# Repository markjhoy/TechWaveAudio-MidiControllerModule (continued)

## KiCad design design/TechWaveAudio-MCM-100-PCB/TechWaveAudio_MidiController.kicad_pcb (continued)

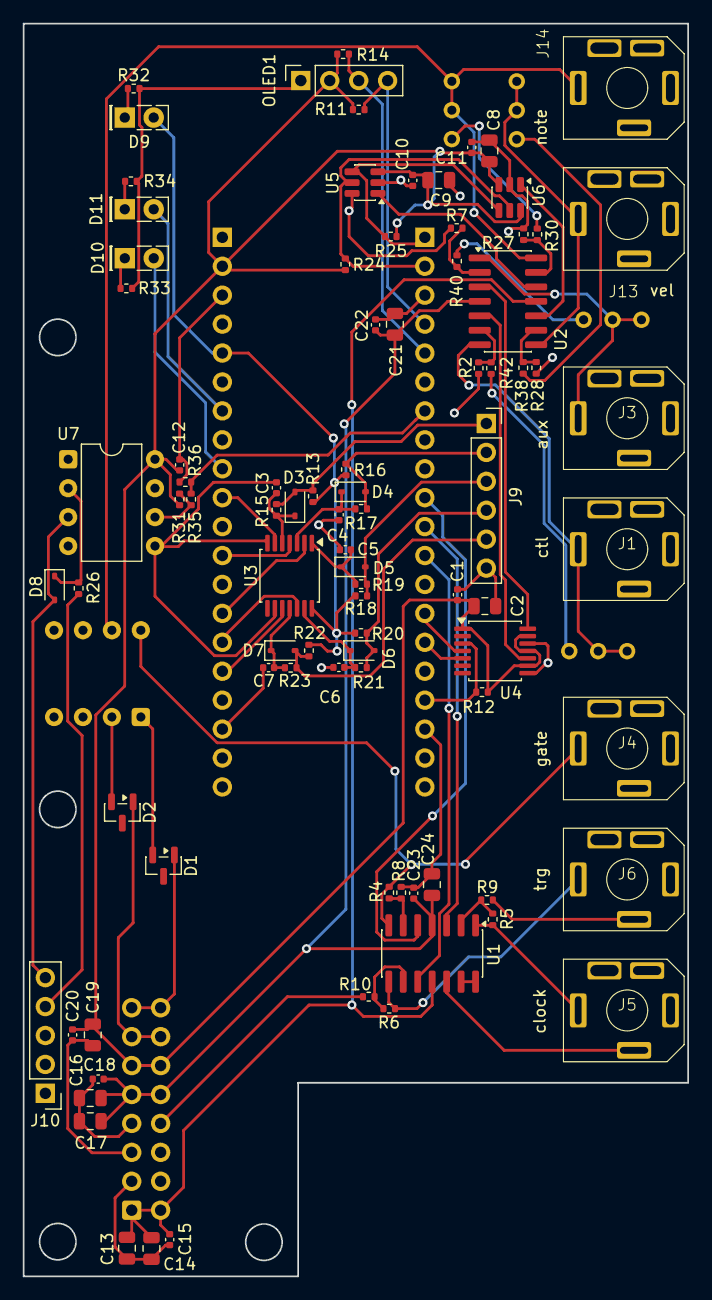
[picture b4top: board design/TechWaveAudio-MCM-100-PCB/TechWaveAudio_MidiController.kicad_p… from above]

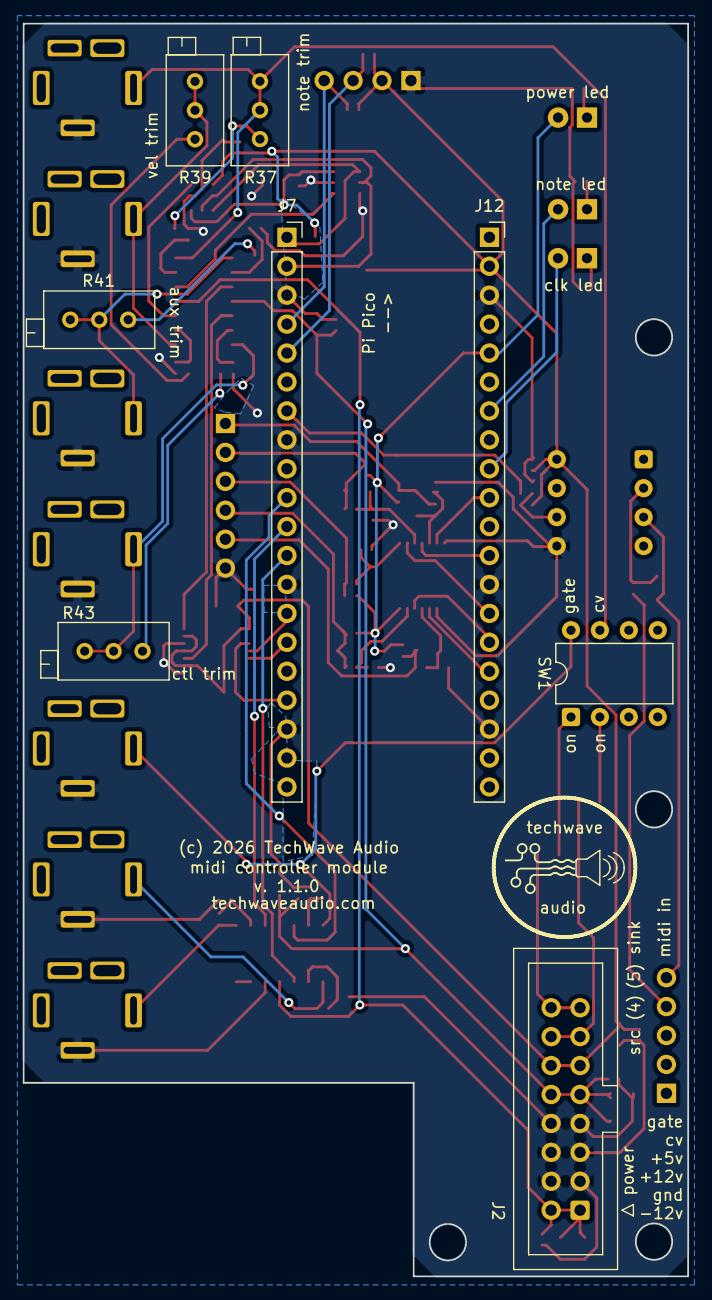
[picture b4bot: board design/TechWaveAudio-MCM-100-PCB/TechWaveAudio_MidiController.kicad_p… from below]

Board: 2 copper layers, 58.3 x 110.0 mm, 96 parts (8 on the bottom side), 67 nets.

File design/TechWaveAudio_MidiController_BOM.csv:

Surface Mount Components,,,,,,
ID,Qty,Description,Package,Mfgr,Mfg Part #,Link
"U5,U6",2,MCP4725 single channel 12 bit I2C DAC,SOIC-14,,,
"U1,U2",2,TL074 op amp,SOIC-14,,,
U4,1,MCP4902 dual channel 8 bit SPI DAC,TSSOP-14,,,
U3,1,40106 Hex Schmitt-trigger inverter,TSSOP-14,,,
"C1,C10,C11,C12,C15,C18 C20,C22,C23",9,100nf capacitor,SMD 0402,,,
"C2,C8,C9,C13,C14,C16,C17,C19,C21,C24",10,10uf capacitor (polarized),SMD 0805,,,
"C3,C4,C5,C6,C7",5,1uf capacitor,SMD 0402,,,
"D1,D2",2,Schottky diode (30v),SOT-23,,,
"D3,D4,D5,D6,D7,D8",6,1N4148 diode,D_SOD-323,,,
"R2 R4,R5,R6,R7,R27,R28,R35",8,resistor 5.1k,SMD 0402,,,
"R8,R9,R10,R36",4,resistor 10k,SMD 0402,,,
"R11,R14,R24,R25,R31",5,resistor 1k,SMD 0402,,,
"R12,R30,R38,R40,R42",5,resistor 4.7k,SMD 0402,,,
"R13,R16,R18,R20,R22",5,resistor 100k,SMD 0402,,,
"R15,R17,R19,R21,R23",5,resistor 220k,SMD 0402,,,
R26,1,resistor 220 ohm,SMD 0402,,,
"R32,R33,R34",3,resistor 330 ohm,SMD 0402,,,
,,,,,,
Through Hole Components,,,,,,
ID,Qty,Description,Mfgr,Mfg Part #,Link,
J2,1,16 pos 2x08 IDC pins (male),Samtec,TST-108-02-T-D,https://mou.sr/4oMjFmU,
"R37,R39,R41,R43",4,1k trim pot,Bourns,3296X-1-102LF,https://mou.sr/44u4OnX,
OLED1,1,1x04 socket connector,Samtec,SSW-104-01-T-S,https://mou.sr/43Qrwqd,
J9,1,1x06 socket connector,Samtec,SSW-106-01-T-S,https://mou.sr/4ahPiPr,
"J7,J12",2,1x20 socket connector,,,,
"J1,J3,J4,J5,J6,J13,J14",7,3.5mm Jack,,,,
SW1,1,4 position DIP switch,TE Connectivity,2454982-3,https://mou.sr/3SZFLqg,
--,1,5 way button,,,,
U7,1,6N137 Optocoupler,LITEON,6N137,https://mou.sr/4eIy9Qa,
D10,1,green LED,Kingbright,WP113GDT,https://mou.sr/4oNpEIp,
J10,1,MIDI jack,,,,
--,1,"0.96"" SSD1306-based I2C OLED",,,,
A1,1,Raspberry Pi Pico,Raspberry Pi,SC0917,https://mou.sr/41kRroA,
D9,1,red LED,Kingbright,WP113IDT,https://mou.sr/4xOIRNK,
D11,1,yellow LED,Kingbright,WP113YDT,https://mou.sr/4xOQVhs,
,,,,,,
Assembly Components,,,,,,
ID,Qty,Description,,,,
--,5,11mm PCB Standoff 3M hole,,,,
--,2,2M nut,,,,
--,2,2M x 8mm screw,,,,
--,6,3M nut,,,,
--,8,3M x 2mm spacer,(3d printed or bought),,,
--,10,3M x 5mm screw,,,,
--,6,3M x 8mm screw,,,,

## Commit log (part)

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2026-06-18 update default last note value
2026-06-23 working production hardware
2026-06-23 correct i2c / spi
2026-06-23 working multicore
2026-06-23 touch ups
2026-06-24 PCB update; cleanups
2026-06-26 doc cleanups and add images
2026-06-26 code documentation
2026-06-27 safe flash i/o; cleanups; multicore fixes
2026-06-27 direct write OledDisplay (no text buffer)
2026-06-27 use bars for display of vel, ctl, aux, etc.
2026-06-27 correct pitch bend range output
2026-06-27 dont highlight title; spinlocks for event queue
2026-06-27 update doc images
2026-06-27 add licensing information
2026-06-28 update copyright
2026-06-28 start of SW design docs
2026-06-28 fix error in ctl/aux output
2026-06-28 cleanups; code documentation
2026-06-28 update pcb; move LEDs and mounting
2026-06-30 hardware docs; cleanups and comments
2026-06-30 complete HW docs
2026-06-30 parts list; update board
2026-06-30 move HW images to docs/images
2026-06-30 added software design docs
2026-06-30 Add version tag, update README
2026-06-30 update README with release path
2026-06-30 add _correct_ releases path :/
